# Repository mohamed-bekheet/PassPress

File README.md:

# PassPress (Hardware Security & BLE Keyboard Project)

**PassPress** is an open hardware and software project featuring a compact hardware password manager and custom Bluetooth Low Energy (BLE) / USB HID keyboard device.

---

## Repository Structure (Monorepo)

This repository is organized as a unified monorepo containing all sub-systems of the project:

```
Pass_Press/
├── passpress-hardware/     # PCB schematics (KiCad), BOM Excel sheet, datasheets, libraries
├── passpress-firmware/     # Embedded C/C++ firmware (STM32F042), USB HID, Bootloader, GUI
├── passpress_mobile_ble/   # Android BLE virtual keyboard app & companion software
├── passpress-huawei-watch/ # Huawei wearable watch companion application
└── README.md               # Root project index (this file)
```

---

## Component Quick Links

1. 🛠️ **[Hardware (`passpress-hardware`)](file:///e:/Personal/Pass_Press/passpress-hardware/README.md)**:
   - KiCad schematics and PCB designs for STM32 and CH32 MCU variants (`kicad-stm`, `kicad-ch32`, `kicad-v2`).
   - Bill of Materials ([Components.xlsx](file:///e:/Personal/Pass_Press/passpress-hardware/Components.xlsx)).
   - IC Datasheets ([datasheets/](file:///e:/Personal/Pass_Press/passpress-hardware/datasheets/)).

2. ⚡ **[Embedded Firmware (`passpress-firmware`)](file:///e:/Personal/Pass_Press/passpress-firmware/README.md)**:
   - STM32F042 C/C++ firmware workspace (`STM_WS`).
   - USB HID driver, Bootloader, Touch sensing (`TOUCHSENSING`), and GUI display engine.

3. 📱 **[Mobile Application (`passpress_mobile_ble`)](file:///e:/Personal/Pass_Press/passpress_mobile_ble/README.md)**:
   - Native Android Virtual BLE Keyboard app (`android/passpress_ble_keyboard`).
   - Setup guide ([ANDROID_SETUP.md](file:///e:/Personal/Pass_Press/passpress_mobile_ble/ANDROID_SETUP.md)).
   - Legacy Web Bluetooth and Python testing tools (`legacy/`).

4. ⌚ **[Huawei Watch App (`passpress-huawei-watch`)](file:///e:/Personal/Pass_Press/passpress-huawei-watch/README.md)**:
   - Huawei smartwatch companion app for HarmonyOS / LiteOS / Huawei Wear Engine.

---

## Project Architecture Summary

```
+------------------------+      BLE / USB      +-------------------------+
|  passpress_mobile_ble  |  ---------------->  |   passpress-hardware    |
|  (Android Companion)   |                     |   (PCB, MCU, Touch, USB)  |
+------------------------+                     +-------------------------+
                                                            |
                                                            v
                                               +-------------------------+
                                               |   passpress-firmware    |
                                               |  (C/C++, USB HID, GUI)  |
                                               +-------------------------+
```

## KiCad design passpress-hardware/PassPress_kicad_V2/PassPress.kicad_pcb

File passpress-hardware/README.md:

# PassPress Hardware (`passpress-hardware`)

Welcome to the **PassPress Hardware** design repository. This directory contains the complete electronic engineering files for the PassPress hardware device, including KiCad schematics, PCB layout files, component libraries, datasheet references, and Bill of Materials (BOM).

---

## Directory Structure

```
passpress-hardware/
├── PassPress_kicad/           # Main base PCB schematic and board layout
├── PassPress_kicad_STM/       # PCB design variant for STM32 microcontroller
├── PassPress_kicad_CH32/      # PCB design variant for CH32 microcontroller
├── PassPress_kicad_CH32_BLE/  # PCB design variant for CH32 BLE microcontroller
├── PassPress_kicad_Combined/  # Combined hardware schematic & PCB layout
├── PassPress_kicad_V2/        # Hardware Revision 2 schematic and layout
├── datasheets/                # Technical IC datasheets & component specifications
├── STM_DOC/                   # STM microcontroller documentation & reference manuals
├── libs_ripos/                # KiCad custom symbol & footprint libraries
├── Components.xlsx            # Master Bill of Materials (BOM) & component list
└── README.md                  # This documentation file
```

---

## Hardware Modules & Schematic Hierarchy

Each KiCad project directory contains structured schematic sheets for specific hardware functional blocks:

- `mcu.kicad_sch` — Main Microcontroller circuit (STM32 / CH32) & pin assignments.
- `power.kicad_sch` — Power management, voltage regulators, and battery/LDO circuit.
- `usb.kicad_sch` — USB Type-C interface, ESD protection, and data line conditioning.
- `antenna.kicad_sch` — Bluetooth LE antenna matching network & RF frontend.
- `INTERFACE.kicad_sch` — User input buttons, touch sensor pads, and display connectors.

---

## Microcontroller Variants

1. **STM32 Variant (`PassPress_kicad_STM`)**:
   - Target MCU: STM32F042 ARM Cortex-M0.
   - Built-in USB 2.0 Full-Speed Crystal-less controller & capacitive touch sensing logic.

2. **CH32 / CH32-BLE Variant (`PassPress_kicad_CH32`, `PassPress_kicad_CH32_BLE`)**:
   - Target MCU: WCH CH32 series microcontroller with integrated BLE transceiver.

---

## Inventory & Component Data

- **Master BOM**: Refer to [Components.xlsx](file:///e:/Personal/Pass_Press/passpress-hardware/Components.xlsx) for part numbers, manufacturer details, and package sizes (e.g. 0603, QFN, QFP).
- **Datasheets**: Refer to the [datasheets/](file:///e:/Personal/Pass_Press/passpress-hardware/datasheets/) directory for hardware datasheets.

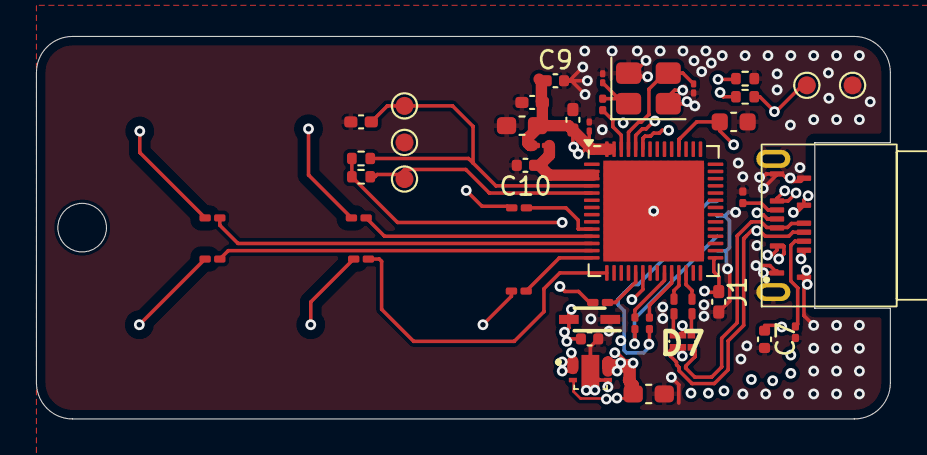
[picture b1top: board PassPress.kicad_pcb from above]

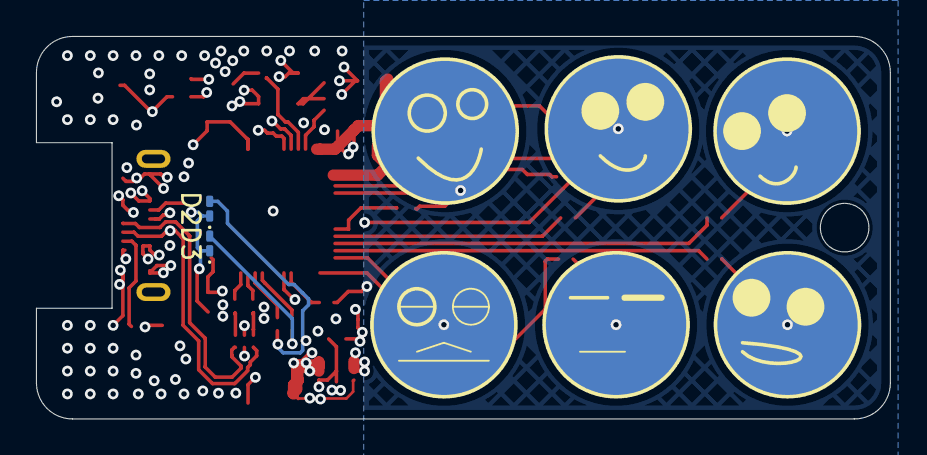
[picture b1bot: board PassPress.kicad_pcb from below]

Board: 4 copper layers, 47.4 x 21.2 mm, 53 parts (8 on the bottom side), 36 nets.

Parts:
C3: 10uF; C_0603_1608Metric_Pad1.08x0.95mm_HandSolder
C4: 0.1u; C_0603_1608Metric
C5, C6, C11, C21: 1u; C_0402_1005Metric_Pad0.74x0.62mm_HandSolder
C7, C9, C10: 0.1uF; C_0402_1005Metric
C8: 10n; C_01005_0402Metric
C13: 22uF; C_0603_1608Metric_Pad1.08x0.95mm_HandSolder
C15, C16: 22pF; C_01005_0402Metric
C20: 4.7uF; C_0402_1005Metric
D1: PESD3V3L1BAF; SOD2512X110N
D2, D3: LED; LED_0201_0603Metric_Pad0.64x0.40mm_HandSolder
D7: PRTR5V0U2F,115; PESD3V3L5UF115
H1: MountingHole; MountingHole_2.7mm
IC2: XC6220B331ER-G
J1: USB_C_GT-USB-8012A
L1: 2n; L_01005_0402Metric
L2: 24nH; L_0201_0603Metric
R1, R2: 5.1K; R_0201_0603Metric
R3, R4, R7, R8: 10K; R_0402_1005Metric
R5, R6: 22R; R_0201_0603Metric_Pad0.64x0.40mm_HandSolder
R9, R10, R11, R12, R13, R14, R15: 510R; R_0201_0603Metric_Pad0.64x0.40mm_HandSolder
R16, R17: 220R; R_0201_0603Metric
TP1: RST; TestPoint_Pad_D1.0mm
TP2: RST-G; TestPoint_Pad_D1.0mm
TP6: TestPoint; TestPoint_Pad_D1.0mm
TP7: BOOT-G; TestPoint_Pad_D1.0mm
TP8: BOOT; TestPoint_Pad_D1.0mm
TP11: TOUCH_PAD_1
TP12: TOUCH_PAD_1; TOUCH_PAD_2
TP13: TOUCH_PAD_1; TOUCH_PAD_3
TP14: TOUCH_PAD_1; TOUCH_PAD_4
TP15: TOUCH_PAD_1; TOUCH_PAD_5
TP16: TOUCH_PAD_1; TOUCH_PAD_6
U6: ESP32-S3; QFN-56-1EP_7x7mm_P0.4mm_EP5.6x5.6mm
X1: 40MHZ; Crystal_SMD_3225-4Pin_3.2x2.5mm

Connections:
5V: C13.1, IC2.3 (CE), IC2.5 (VIN_1), IC2.6 (VIN_2), J1.A4 (VBUS), J1.A9 (VBUS), J1.B4 (VBUS), J1.B9 (VBUS)
+3.3V: C3.1, C4.1, C5.1, C6.1, C7.1, C8.1, C9.1, C11.1, C20.1, D1.2 (K2), D7.5 (supply_voltage), IC2.1 (VOUT_1), IC2.2 (VOUT_2), L1.1, R3.1, R4.1, R8.1, TP6.1, U6.20 (VDD3P3_RTC), U6.29 (VDD_SPI), U6.46 (VDD3P3_CPU), U6.55 (VDDA), U6.56 (VDDA)
/MCU/BOOT0: R4.2, TP8.1, U6.5 (GPIO0/BOOT)
/MCU/D+: R5.1, U6.26 (GPIO20/USB_D+/ADC2_CH9)
/MCU/D-: R6.1, U6.25 (GPIO19/USB_D-/ADC2_CH8)
/MCU/LED1-B: R16.2, U6.24 (GPIO18/ADC2_CH7)
/MCU/LED2-G: R17.2, U6.23 (GPIO17/ADC2_CH6)
/MCU/PRESS1: R9.2, TP11.1
/MCU/PRESS2: R10.2, TP12.1
/MCU/PRESS3: R11.2, TP13.1
/MCU/PRESS4: R12.2, TP14.1
/MCU/PRESS5: R13.2, TP15.1
/MCU/PRESS6: R14.2, TP16.1
/MCU/RST: C21.1, R3.2, TP1.1, U6.4 (CHIP_PU/RESET)
/MCU/XTAL_N: C16.1, U6.53 (XTAL_N), X1.3
/MCU/XTAL_P: C15.1, L2.1, X1.1
/USB-C/ESD_USB_D+: D7.3 (input/output_2_1), J1.A7 (D-), J1.B7 (D-)
/USB-C/ESD_USB_D-: D7.1 (input/output_1_1), J1.A6 (D+), J1.B6 (D+)
/USB-C/USB_D+: D7.4 (input/output_2_2), R5.2
/USB-C/USB_D-: D7.6 (input/output_1_2), R6.2
GND: C3.2, C4.2, C5.2, C6.2, C7.2, C8.2, C9.2, C10.2, C11.2, C13.2, C15.2, C16.2, C20.2, C21.2, D1.1 (K1), D2.1 (K), D3.1 (K), D7.2 (ground), IC2.4 (VSS), IC2.7 (EP), J1.A1 (GND), J1.A12 (GND), J1.B1 (GND), J1.B12 (GND), J1.S1 (SHIELD), R1.2, R2.2, R7.2, TP2.1, TP7.1, U6.57 (GND), X1.2, X1.4
unnamed: D2.2 (A), R16.1
unnamed: D3.2 (A), R17.1
unnamed: J1.A5 (CC1), R2.1
unnamed: J1.B5 (CC2), R1.1
unnamed: R9.1, U6.10 (GPIO5/ADC1_CH4)
unnamed: R10.1, U6.11 (GPIO6/ADC1_CH5)
unnamed: R11.1, U6.12 (GPIO7/ADC1_CH6)
unnamed: R12.1, U6.13 (GPIO8/ADC1_CH7)
unnamed: R13.1, U6.14 (GPIO9/ADC1_CH8)
unnamed: R14.1, U6.15 (GPIO10/ADC1_CH9)
unnamed: R15.1, U6.19 (GPIO14/ADC2_CH3)
unnamed: R8.2, U6.51 (GPIO45)
unnamed: R7.1, U6.52 (GPIO46)
unnamed: L2.2, U6.54 (XTAL_P)
VDD3P3: C10.1, L1.2, U6.2 (VDD3P3), U6.3 (VDD3P3)

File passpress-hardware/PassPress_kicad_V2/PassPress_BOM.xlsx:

Id | Designator | Footprint | Quantity | Designation | MNF PART NUMBER
1 | C13 | C_0603_1608Metric_Pad1.08x0.95mm_HandSolder | 1 | 22uF | C59461
2 | C14,C4,C10,C9,C7 | C_0402_1005Metric | 1 | 0.1uF | C1525
3 | C16,C15 | C_01005_0402Metric | 2 | 22pF | C1555
4 | C20 | C_0402_1005Metric | 1 | 4.7uF | C23733
5 | C3 | C_0603_1608Metric_Pad1.08x0.95mm_HandSolder | 1 | 10uF | C19702
6 | C5,C21,C11,C6 | C_0402_1005Metric_Pad0.74x0.62mm_HandSolder | 4 | 1uF | C52923
7 | C8 | C_01005_0402Metric | 1 | 10nF | C15195
8 | D1 | SOD2512X110N | 1 | PESD3V3L1BAF | C552512
9 | D3 | LED_0201_0603Metric_Pad0.64x0.40mm_HandSolder | 2 | LED | C3646921
10 | D2 | LED_0201_0603Metric_Pad0.64x0.40mm_HandSolder | 2 | LED | C3646922
11 | D7 | PESD3V3L5UF115 | 1 | PRTR5V0U2F,115 | C2937001
12 | IC2 | XC6220B331ER-G | 1 | XC6220B331ER-G | C3013657
13 | J1 | USB_C_GT-USB-8012A | 1 | USB_C_GT-USB-8012A | C2982483
14 | L1 | L_01005_0402Metric | 1 | 2n | C18216
15 | L2 | L_0201_0603Metric | 1 | 24nH | C206441
16 | R1,R2 | R_0201_0603Metric | 2 | 5.1K | C163490
17 | R14,R12,R10,R15,R9,R11,R13 | R_0201_0603Metric_Pad0.64x0.40mm_HandSolder | 7 | 510R | C57784
18 | R16,R17 | R_0201_0603Metric | 2 | 220R | C144009
19 | R3,R8,R7,R4 | R_0402_1005Metric | 4 | 10K | C25744
20 | R5,R6 | R_0201_0603Metric_Pad0.64x0.40mm_HandSolder | 2 | 22R | C100162
21 | U6 | QFN-56-1EP_7x7mm_P0.4mm_EP5.6x5.6mm | 1 | ESP32-S3FH4R2 | C3013940
22 | X1 | Crystal_SMD_3225-4Pin_3.2x2.5mm | 1 | XL2EL89CPI-111YLC-40M | C5444549

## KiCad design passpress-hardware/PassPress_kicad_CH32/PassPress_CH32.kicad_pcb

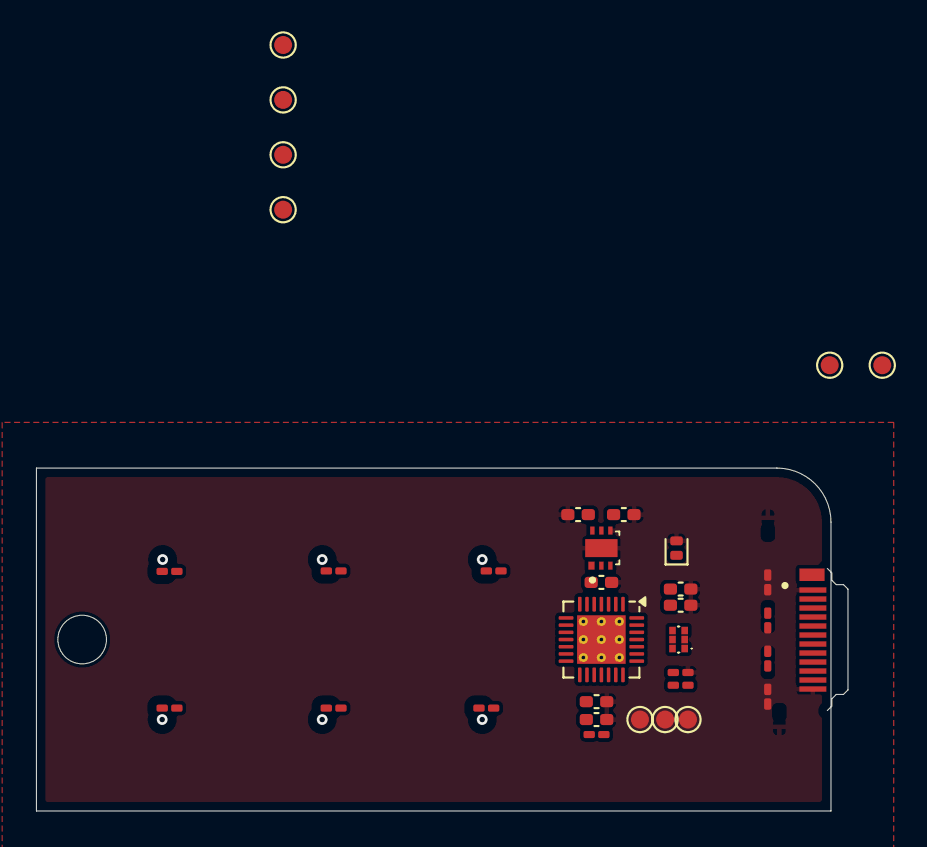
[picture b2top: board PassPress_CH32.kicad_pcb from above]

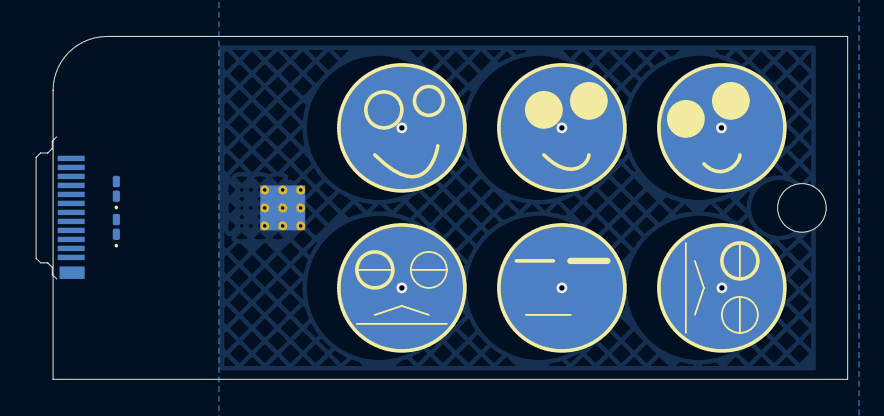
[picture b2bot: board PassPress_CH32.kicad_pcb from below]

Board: 4 copper layers, 45.1 x 19.0 mm, 43 parts (8 on the bottom side), 29 nets, no tracks yet.

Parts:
C3, C20: 4.7uF; C_0402_1005Metric_Pad0.74x0.62mm_HandSolder
C5, C6: 0.1uF; C_0402_1005Metric_Pad0.74x0.62mm_HandSolder
C7: 10n; C_0402_1005Metric_Pad0.74x0.62mm_HandSolder
C11: 1uF; C_0402_1005Metric_Pad0.74x0.62mm_HandSolder
C13: 22uF; C_0402_1005Metric_Pad0.74x0.62mm_HandSolder
D2: LED-R; LED_0201_0603Metric_Pad0.64x0.40mm_HandSolder
D3: LED-G; LED_0201_0603Metric_Pad0.64x0.40mm_HandSolder
D4: PESD5V0V1BL,315; D_SOD-882D
D7: PRTR5V0U2F,115; PESD3V3L5UF115
H1: MountingHole; MountingHole_2.7mm
IC2: XC6220B331ER-G
J1: U261-241N-4BS60; XKB_U261-241N-4BS60_USB_C
R2, R7, R8, R9, R10, R11, R12, R13: 5.1K; R_0201_0603Metric_Pad0.64x0.40mm_HandSolder
R3, R4, R5: 10K; R_0201_0603Metric_Pad0.64x0.40mm_HandSolder
R6, R16: 220R; R_0201_0603Metric_Pad0.64x0.40mm_HandSolder
TP1: RST; TestPoint_Pad_D1.0mm
TP2: RST-G; TestPoint_Pad_D1.0mm
TP5: 3.3V; TestPoint_Pad_D1.0mm
TP6: TestPoint; TestPoint_Pad_D1.0mm
TP7: BOOT-G; TestPoint_Pad_D1.0mm
TP8: BOOT; TestPoint_Pad_D1.0mm
TP11: TOUCH_PAD_1; TOUCH_PAD_1_7mm
TP12: TOUCH_PAD_1; TOUCH_PAD_2_7mm
TP13: TOUCH_PAD_1; TOUCH_PAD_3_7mm
TP14: TOUCH_PAD_1; TOUCH_PAD_4_7mm
TP15: TOUCH_PAD_1; TOUCH_PAD_5_7mm
TP16: TOUCH_PAD_1; TOUCH_PAD_6_7mm
TP19: SWDIO; TestPoint_Pad_D1.0mm
TP20: SWCLK; TestPoint_Pad_D1.0mm
TP21: GND; TestPoint_Pad_D1.0mm
U2: CH32X035G8U6; WQFN-28-1EP_4x4mm_P0.4mm_EP2.7x2.7mm_ThermalVias

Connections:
5V: C3.1, C13.1, D4.1 (K), IC2.3 (CE), IC2.5 (VIN_1), IC2.6 (VIN_2), J1.A4 (VBUS), J1.A9 (VBUS), J1.B4 (VBUS), J1.B9 (VBUS)
+3.3V: C5.1, C11.1, C20.1, D7.5 (supply_voltage), IC2.1 (VOUT_1), IC2.2 (VOUT_2), R3.1, R5.1, TP5.1, TP6.1, TP7.1, U2.2 (VDD)
/MCU/BOOT0: R4.1, R5.2, TP8.1, TP20.1, U2.24 (PC19/DCK)
/MCU/D+: D7.4 (input/output_2_2), U2.27 (PC10/PC17/UDP)
/MCU/D-: D7.6 (input/output_1_2), U2.26 (PC11/PC16/UDM)
/MCU/LED1-B: R16.2, U2.3 (PC0)
/MCU/LED2-G: R6.2, U2.16 (PB1/PB5)
/MCU/P1: R8.1, U2.6 (PA1)
/MCU/P2: R9.1, U2.7 (PA2)
/MCU/P3: R10.1, U2.8 (PA3)
/MCU/P4: R11.1, U2.9 (PA4)
/MCU/P5: R12.1, U2.11 (PA6)
/MCU/P6: R13.1, U2.10 (PA5)
/MCU/PRESS1: R8.2, TP11.1
/MCU/PRESS2: R9.2, TP12.1
/MCU/PRESS3: R10.2, TP13.1
/MCU/PRESS4: R11.2, TP14.1
/MCU/PRESS5: R12.2, TP15.1
/MCU/PRESS6: R13.2, TP16.1
/MCU/RST: C6.1, R3.2, TP1.1, U2.4 (PC3)
/MCU/SWDIO: TP19.1, U2.25 (PC18/DIO)
/USB-C/ESD_USB_D+: D7.3 (input/output_2_1), J1.A7 (D-), J1.B7 (D-)
/USB-C/ESD_USB_D-: D7.1 (input/output_1_1), J1.A6 (D+), J1.B6 (D+)
GND: C3.2, C5.2, C6.2, C7.2, C11.2, C13.2, C20.2, D2.1 (K), D3.1 (K), D4.2 (A), D7.2 (ground), IC2.4 (VSS), IC2.7 (EP), J1.A1 (GND), J1.A12 (GND), J1.B1 (GND), J1.B12 (GND), R2.2, R4.2, R7.2, TP2.1, TP21.1, U2.29 (GND)
unnamed: D2.2 (A), R6.1
unnamed: D3.2 (A), R16.1
unnamed: J1.A5 (CC1), R2.1
unnamed: J1.B5 (CC2), R7.1
unnamed: C7.1, U2.5 (PA0)

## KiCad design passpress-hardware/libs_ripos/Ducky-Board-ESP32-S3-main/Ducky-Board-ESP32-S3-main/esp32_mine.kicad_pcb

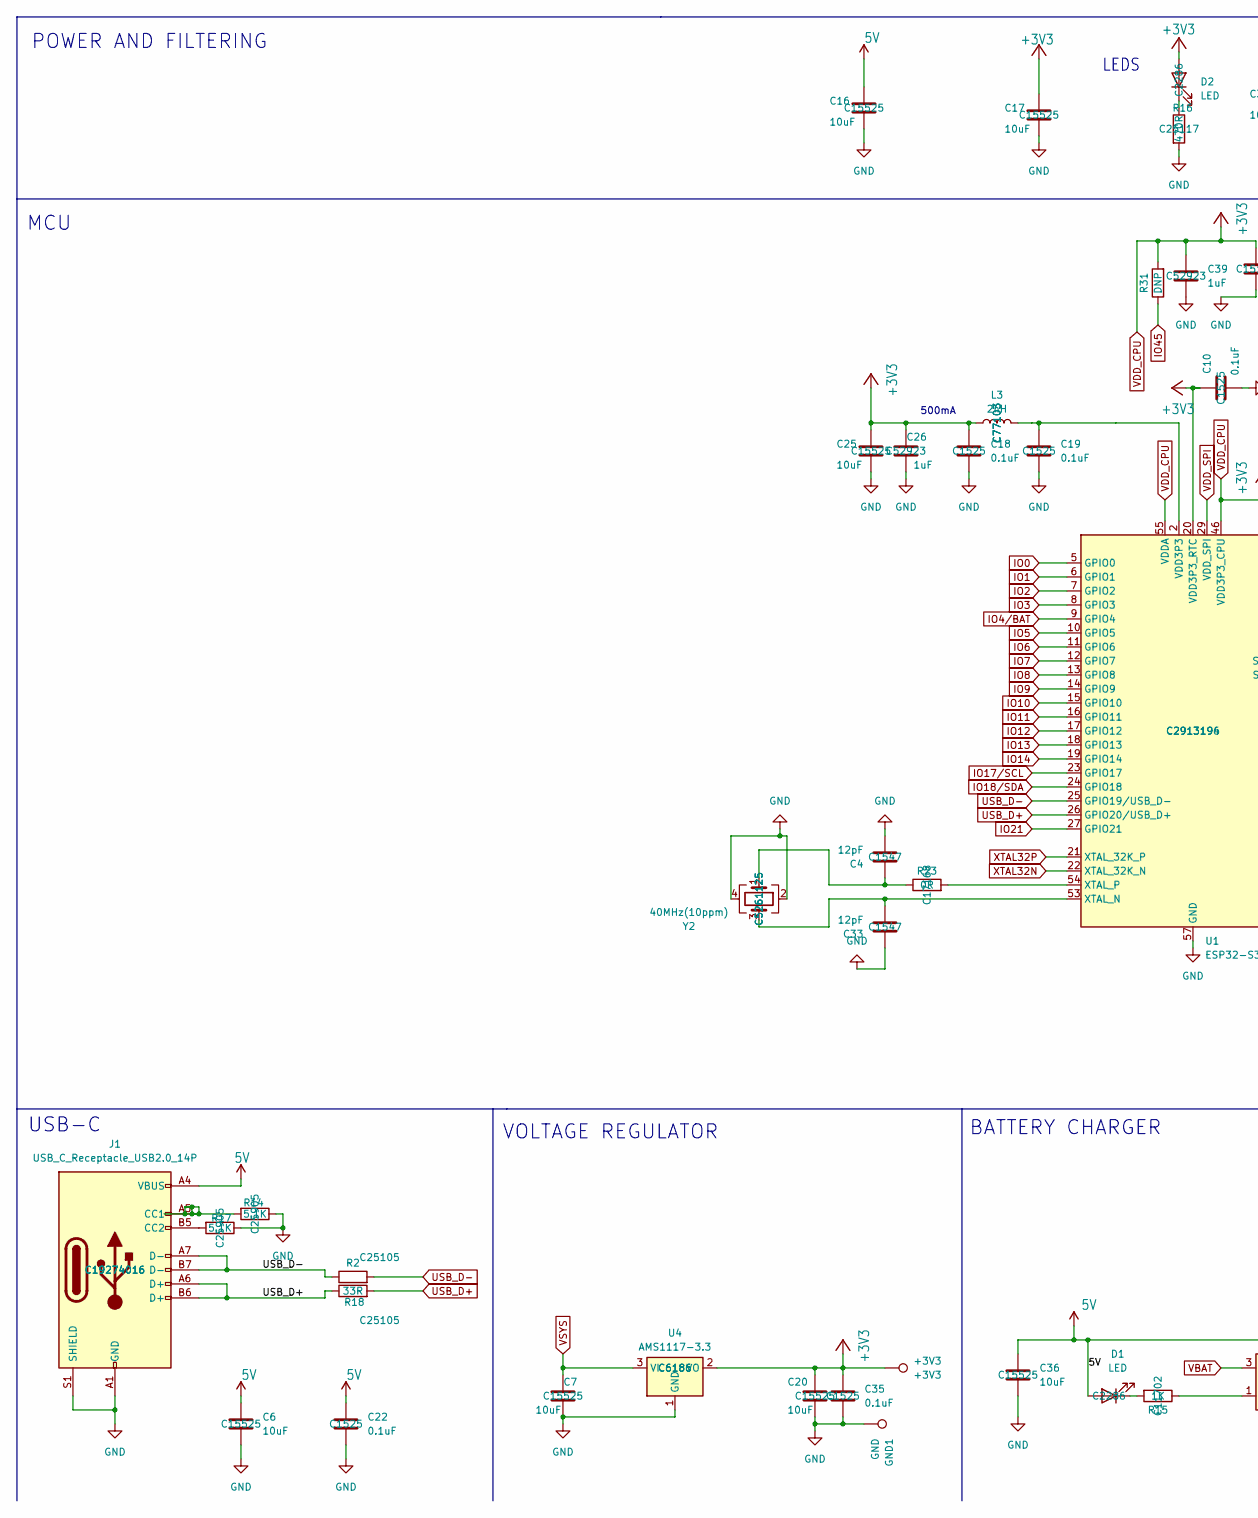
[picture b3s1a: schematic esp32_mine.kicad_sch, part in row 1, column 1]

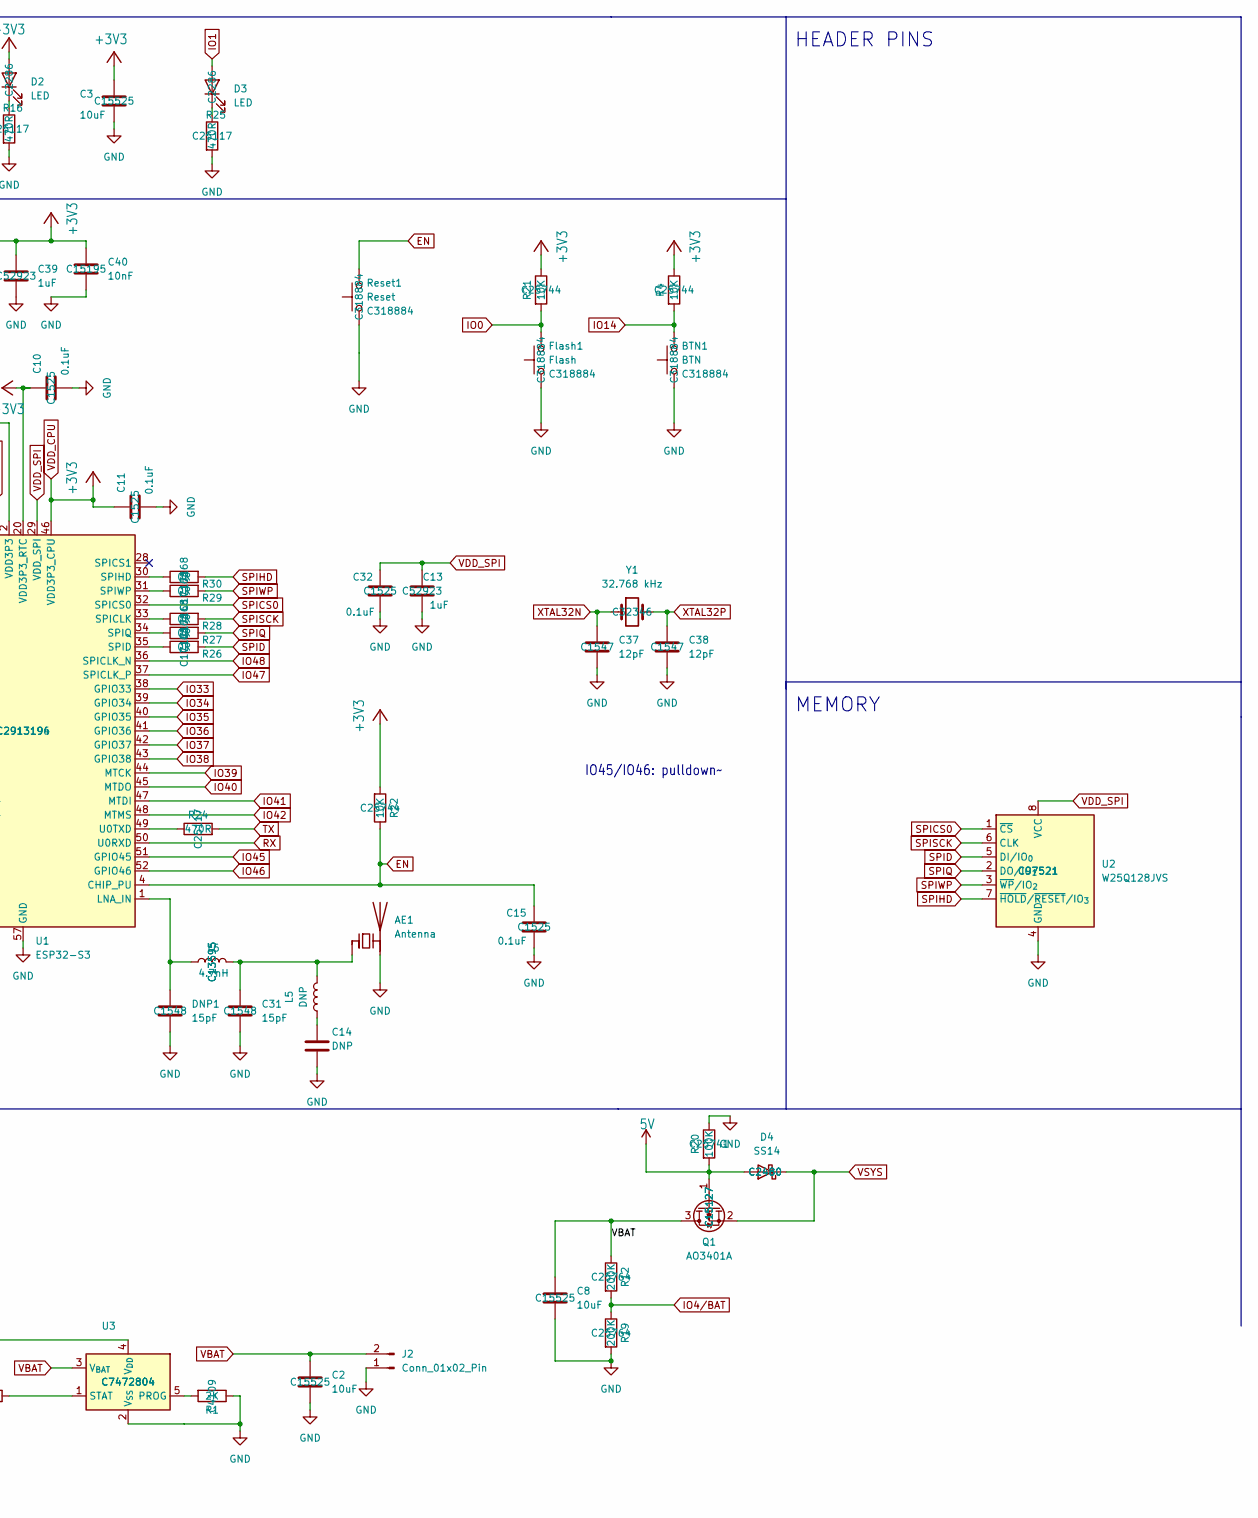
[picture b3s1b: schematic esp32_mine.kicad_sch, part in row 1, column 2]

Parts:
+3V3: +3V3; TestPoint_Pad_D1.0mm
AE1: Antenna; Texas_SWRA117D_2.4GHz_Left
BTN1: BTN; SW_Push_1P1T_XKB_TS-1187A; MNF PART NUMBER C318884; LCSC C318884
C2, C3, C6, C7, C8, C16, C17, C20, C25, C36: 10uF; C_0402_1005Metric; MNF PART NUMBER C15525; LCSC C15525
C4, C33, C37, C38: 12pF; C_0402_1005Metric; MNF PART NUMBER C1547; LCSC C1547
C10, C11, C15, C18, C19, C22, C32, C35: 0.1uF; C_0402_1005Metric; MNF PART NUMBER C1525; LCSC C1525
C13, C26, C39: 1uF; C_0402_1005Metric; MNF PART NUMBER C52923; LCSC C52923
C14: DNP; C_0402_1005Metric
C31: 15pF; C_0402_1005Metric; MNF PART NUMBER C1548; LCSC C1548
C40: 10nF; C_0402_1005Metric; MNF PART NUMBER C15195; LCSC C15195
D1, D2, D3: LED; LED_0603_1608Metric; MNF PART NUMBER C2286; LCSC C2286
D4: SS14; D_SMA; MNF PART NUMBER C2480; LCSC C2480
DNP1: 15pF; C_0402_1005Metric; MNF PART NUMBER C1548; LCSC C1548
Flash1: Flash; SW_Push_1P1T_XKB_TS-1187A; MNF PART NUMBER C318884; LCSC C318884
GND1: GND; TestPoint_Pad_D1.0mm
J1: USB_C_Receptacle_USB2.0_14P; USB_C_Receptacle_HCTL_HC-TYPE-C-16P-01A; MNF PART NUMBER C19274016; LCSC C19274016
J2: Conn_01x02_Pin; PinSocket_1x02_P2.54mm_Vertical
L3: 2nH; L_0402_1005Metric; MNF PART NUMBER C77103; LCSC C77103
L5: DNP; L_0402_1005Metric
L6: 4.7nH; L_0402_1005Metric; MNF PART NUMBER C13595; LCSC C13595
Q1: AO3401A; SOT-23; MNF PART NUMBER C15127; LCSC C15127
R1: 2K; R_0402_1005Metric; MNF PART NUMBER C4109; LCSC C4109
R2, R18: 33R; R_0402_1005Metric; MNF PART NUMBER C25105; LCSC C25105
R4, R21, R22: 10K; R_0402_1005Metric; MNF PART NUMBER C25744; LCSC C25744
R12, R19: 200K; R_0402_1005Metric; MNF PART NUMBER C25764; LCSC C25764
R14, R17: 5.1K; R_0402_1005Metric; MNF PART NUMBER C25905; LCSC C25905
R15: 1K; R_0402_1005Metric; MNF PART NUMBER C11702; LCSC C11702
R16, R24, R25: 470R; R_0402_1005Metric; MNF PART NUMBER C25117; LCSC C25117
R20: 100K; R_0402_1005Metric; MNF PART NUMBER C25741; LCSC C25741
R23, R26, R27, R28, R29, R30: 0R; R_0402_1005Metric; MNF PART NUMBER C17168; LCSC C17168
R31: DNP; R_0402_1005Metric
Reset1: Reset; SW_Push_1P1T_XKB_TS-1187A; MNF PART NUMBER C318884; LCSC C318884
U1: ESP32-S3; QFN-56-1EP_7x7mm_P0.4mm_EP4x4mm; MNF PART NUMBER C2913196; LCSC C2913194
U2: W25Q128JVS; SOIC-8_5.3x5.3mm_P1.27mm; MNF PART NUMBER C97521; LCSC C97521
U3: MCP73831-2-OT; SOT-23-5; MNF PART NUMBER C7472804; LCSC C7472804
U4: AMS1117-3.3; SOT-223-3_TabPin2; MNF PART NUMBER C6186; LCSC C6186
Y1: 32.768 kHz; Crystal_SMD_3215-2Pin_3.2x1.5mm; MNF PART NUMBER C32346; LCSC C32346
Y2: 40MHz(10ppm); Crystal_SMD_2520-4Pin_2.5x2.0mm; MNF PART NUMBER C5261125; LCSC C5261125

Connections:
5V: C6.1, C16.1, C22.1, C36.1, D1.2 (A), D4.2 (A), J1.A4 (VBUS), J1.A9 (VBUS), J1.B4 (VBUS), J1.B9 (VBUS), Q1.1 (G), R20.2, U3.4 (V_{DD}); also elsewhere on the board
EN: C15.1, R22.1, Reset1.2, U1.4 (CHIP_PU)
GND: AE1.2 (PCB_Trace), BTN1.1, C2.2, C3.2, C4.2, C6.2, C7.2, C8.2, C10.2, C11.2, C13.2, C14.2, C15.2, C16.2, C17.2, C18.2, C19.2, C20.2, C22.2, C25.2, C26.2, C31.2, C32.2, C33.1, C35.2, C36.2, C37.2, C38.2, C39.2, C40.2, DNP1.2, Flash1.1, GND1.1, J1.A1 (GND), J1.A12 (GND), J1.B1 (GND), J1.B12 (GND), J1.S1 (SHIELD), J2.1, R1.1, R14.1, R16.2, R17.1, R19.2, R20.1, R25.2, Reset1.1, U1.57 (GND), U2.4 (GND), U3.2 (V_{SS}), U4.1 (GND), Y2.2, Y2.4; also elsewhere on the board
IO0: Flash1.2, R21.2, U1.5 (GPIO0); also elsewhere on the board
IO1: D3.2 (A), U1.6 (GPIO1)
IO2: U1.7 (GPIO2); also elsewhere on the board
IO3: U1.8 (GPIO3); also elsewhere on the board
IO4/BAT: R12.2, R19.1, U1.9 (GPIO4)
IO5: U1.10 (GPIO5); also elsewhere on the board
IO6: U1.11 (GPIO6); also elsewhere on the board
IO7: U1.12 (GPIO7); also elsewhere on the board
IO8: U1.13 (GPIO8); also elsewhere on the board
IO9: U1.14 (GPIO9); also elsewhere on the board
IO10: U1.15 (GPIO10); also elsewhere on the board
IO11: U1.16 (GPIO11); also elsewhere on the board
IO12: U1.17 (GPIO12); also elsewhere on the board
IO13: U1.18 (GPIO13); also elsewhere on the board
IO14: BTN1.2, R4.2, U1.19 (GPIO14); also elsewhere on the board
IO17/SCL: U1.23 (GPIO17); also elsewhere on the board
IO18/SDA: U1.24 (GPIO18); also elsewhere on the board
IO21: U1.27 (GPIO21); also elsewhere on the board
IO33: U1.38 (GPIO33); also elsewhere on the board
IO34: U1.39 (GPIO34); also elsewhere on the board
IO35: U1.40 (GPIO35); also elsewhere on the board
IO36: U1.41 (GPIO36); also elsewhere on the board
IO37: U1.42 (GPIO37); also elsewhere on the board
IO38: U1.43 (GPIO38); also elsewhere on the board
IO39: U1.44 (MTCK); also elsewhere on the board
IO40: U1.45 (MTDO); also elsewhere on the board
IO41: U1.47 (MTDI); also elsewhere on the board
IO42: U1.48 (MTMS); also elsewhere on the board
IO45: R31.1, U1.51 (GPIO45); also elsewhere on the board
IO46: U1.52 (GPIO46); also elsewhere on the board
IO47: U1.37 (SPICLK_P); also elsewhere on the board
IO48: U1.36 (SPICLK_N); also elsewhere on the board
unnamed: AE1.1 (FEED), C31.1, L5.2, L6.2
unnamed: C4.1, R23.1, Y2.1
unnamed: C14.1, L5.1
unnamed: C19.1, L3.2, U1.2 (VDD3P3), U1.3 (VDD3P3)
unnamed: D1.1 (K), R15.2
unnamed: D2.1 (K), R16.1
unnamed: D3.1 (K), R25.1
unnamed: J1.A5 (CC1), R14.2
unnamed: J1.B5 (CC2), R17.2
unnamed: DNP1.1, L6.1, U1.1 (LNA_IN)
unnamed: R28.1, U1.33 (SPICLK)
unnamed: R26.1, U1.35 (SPID)
unnamed: R30.1, U1.30 (SPIHD)
unnamed: R27.1, U1.34 (SPIQ)
unnamed: R29.1, U1.31 (SPIWP)
unnamed: R24.1, U1.49 (U0TXD)
unnamed: C33.2, U1.53 (XTAL_N), Y2.3
unnamed: R23.2, U1.54 (XTAL_P)
unnamed: R1.2, U3.5 (PROG)
unnamed: R15.1, U3.1 (STAT)
RX: U1.50 (U0RXD); also elsewhere on the board
SPICS0: U1.32 (SPICS0), U2.1 (~CS)
SPID: R26.2, U2.5 (DI/IO_{0})
SPIHD: R30.2, U2.7 (~HOLD/~RESET/IO_{3})
SPIQ: R27.2, U2.2 (DO/IO_{1})
SPISCK: R28.2, U2.6 (CLK)
SPIWP: R29.2, U2.3 (~WP/IO_{2})
TX: R24.2; also elsewhere on the board
USB_D+: J1.A6 (D+), J1.B6 (D+), R18.1, R18.2, U1.26 (GPIO20/USB_D+)
USB_D-: J1.A7 (D-), J1.B7 (D-), R2.1, R2.2, U1.25 (GPIO19/USB_D-)
VBAT: C2.1, C8.1, J2.2, Q1.3 (D), R12.1, U3.3 (V_{BAT})
VDD_CPU: +3V3.1, C3.1, C10.1, C11.1, C17.1, C18.1, C20.1, C25.1, C26.1, C35.1, C39.1, C40.1, D2.2 (A), L3.1, R4.1, R21.1, R22.2, R31.2, U1.20 (VDD3P3_RTC), U1.46 (VDD3P3_CPU), U1.55 (VDDA), U1.56 (VDDA), U4.2 (VO); also elsewhere on the board
VDD_SPI: C13.1, C32.1, U1.29 (VDD_SPI), U2.8 (VCC)
VSYS: C7.1, D4.1 (K), Q1.2 (S), U4.3 (VI)
XTAL32N: C37.1, U1.22 (XTAL_32K_N), Y1.1
XTAL32P: C38.1, U1.21 (XTAL_32K_P), Y1.2

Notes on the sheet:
BATTERY CHARGER
VOLTAGE REGULATOR
500mA
LEDS
MCU
HEADER PINS
MEMORY
POWER AND FILTERING
IO45/IO46: pulldown~~{}
USB-C

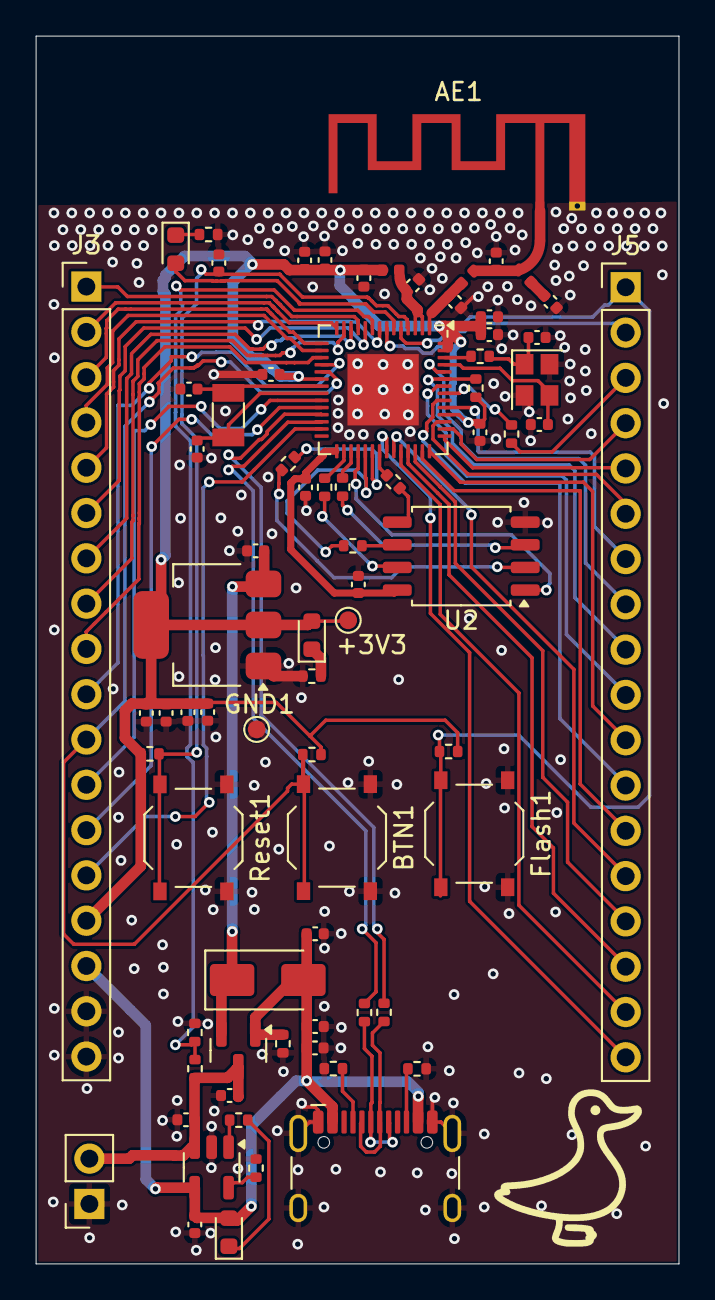
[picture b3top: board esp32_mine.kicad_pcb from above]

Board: 2 copper layers, 36.0 x 68.8 mm, 75 parts (0 on the bottom side), 71 nets.

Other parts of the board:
J3, J5: Conn_01x18_Pin; PinHeader_1x18_P2.54mm_Vertical

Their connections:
5V: J3.16; also elsewhere on the board
GND: J3.17, J3.18; also elsewhere on the board
IO0: J5.1; also elsewhere on the board
IO2: J5.2; also elsewhere on the board
IO3: J3.5; also elsewhere on the board
IO5: J3.6; also elsewhere on the board
IO6: J3.1; also elsewhere on the board
IO7: J3.7; also elsewhere on the board
IO8: J3.8; also elsewhere on the board
IO9: J3.2; also elsewhere on the board
IO10: J3.3; also elsewhere on the board
IO11: J3.4; also elsewhere on the board
IO12: J3.9; also elsewhere on the board
IO13: J3.10; also elsewhere on the board
IO14: J3.11; also elsewhere on the board
IO17/SCL: J3.12; also elsewhere on the board
IO18/SDA: J3.13; also elsewhere on the board
IO21: J3.14; also elsewhere on the board
IO33: J5.17; also elsewhere on the board
IO34: J5.16; also elsewhere on the board
IO35: J5.15; also elsewhere on the board
IO36: J5.13; also elsewhere on the board
IO37: J5.11; also elsewhere on the board
IO38: J5.5; also elsewhere on the board
IO39: J5.4; also elsewhere on the board
IO40: J5.6; also elsewhere on the board
IO41: J5.7; also elsewhere on the board
IO42: J5.12; also elsewhere on the board
IO45: J5.9; also elsewhere on the board
IO46: J5.8; also elsewhere on the board
IO47: J5.14; also elsewhere on the board
IO48: J5.18; also elsewhere on the board
RX: J5.10; also elsewhere on the board
TX: J5.3; also elsewhere on the board
VDD_CPU: J3.15; also elsewhere on the board

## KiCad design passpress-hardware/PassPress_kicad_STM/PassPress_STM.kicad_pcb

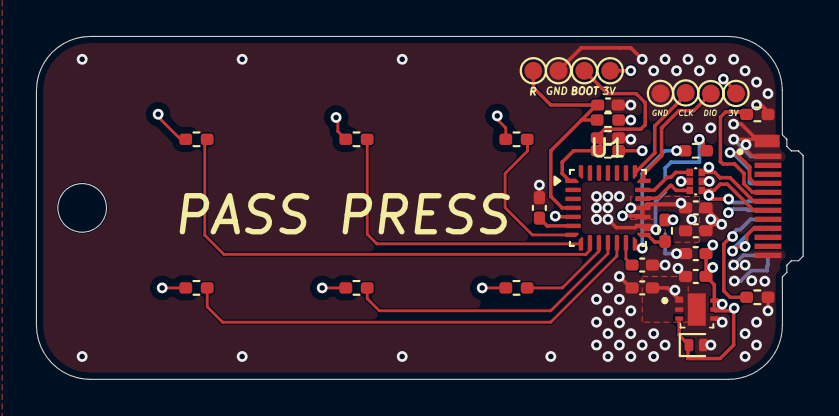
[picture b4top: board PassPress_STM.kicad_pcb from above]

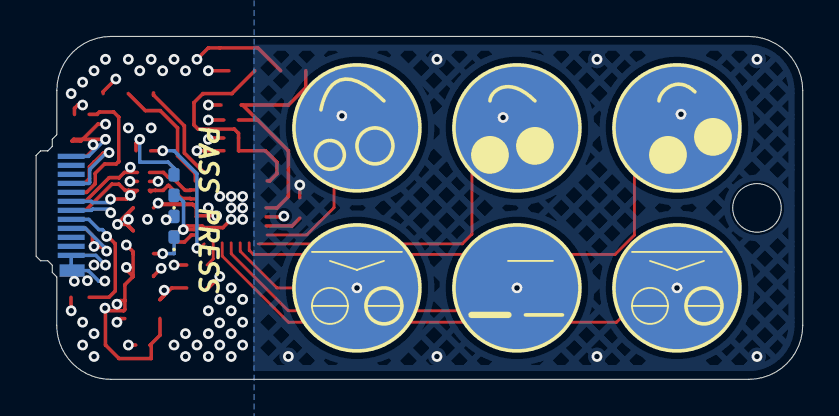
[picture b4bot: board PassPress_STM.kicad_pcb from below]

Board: 4 copper layers, 42.6 x 19.0 mm, 43 parts (8 on the bottom side), 31 nets.

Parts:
C3, C4, C20: 4.7uF; C_0402_1005Metric_Pad0.74x0.62mm_HandSolder
C6, C15: 0.1uF; C_0402_1005Metric_Pad0.74x0.62mm_HandSolder
C7, C8: 10n; C_0402_1005Metric_Pad0.74x0.62mm_HandSolder
C13: 22uF; C_0402_1005Metric_Pad0.74x0.62mm_HandSolder
D2: PESD5V0V1BL,315; D_SOD-882D
D4: LED-G; LED_0402_1005Metric_Pad0.77x0.64mm_HandSolder
D5: LED-R; LED_0402_1005Metric_Pad0.77x0.64mm_HandSolder
D7: PRTR5V0U2F,115; PESD3V3L5UF115
H1: MountingHole; MountingHole_2.7mm
IC2: XC6220B331ER-G
J1: U261-241N-4BS60; XKB_U261-241N-4BS60_USB_C
R1, R14: 220R; R_0402_1005Metric_Pad0.72x0.64mm_HandSolder
R2, R6, R7, R8, R9, R10, R11, R12: 5.1K; R_0402_1005Metric_Pad0.72x0.64mm_HandSolder
R3, R4, R5: 10K; R_0402_1005Metric_Pad0.72x0.64mm_HandSolder
TP1: RST; TestPoint_Pad_D1.0mm
TP2: RST-G; TestPoint_Pad_D1.0mm
TP5: 3.3V; TestPoint_Pad_D1.0mm
TP7: BOOT-G; TestPoint_Pad_D1.0mm
TP8: BOOT; TestPoint_Pad_D1.0mm
TP11: TOUCH_PAD_1; TOUCH_PAD_1_7mm
TP12: TOUCH_PAD_1; TOUCH_PAD_2_7mm
TP13: TOUCH_PAD_1; TOUCH_PAD_3_7mm
TP14: TOUCH_PAD_1; TOUCH_PAD_4_7mm
TP15: TOUCH_PAD_1; TOUCH_PAD_5_7mm
TP16: TOUCH_PAD_1; TOUCH_PAD_6_7mm
TP19: SWDIO; TestPoint_Pad_D1.0mm
TP20: SWCLK; TestPoint_Pad_D1.0mm
TP21: GND; TestPoint_Pad_D1.0mm
U1: STM32F042G6U6TR; QFN-28_4x4mm_P0.5mm

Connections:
5V: C3.1, C13.1, D2.1 (K), IC2.3 (CE), IC2.5 (VIN_1), IC2.6 (VIN_2), J1.A4 (VBUS), J1.A9 (VBUS), J1.B4 (VBUS), J1.B9 (VBUS)
+3.3V: C4.1, C15.1, C20.1, D7.5 (supply_voltage), IC2.1 (VOUT_1), IC2.2 (VOUT_2), R3.1, R5.1, TP5.1, TP7.1, U1.5 (VDDA), U1.17 (VDD), U1.18 (VDDIO2)
/MCU/BOOT0: R4.1, R5.2, TP8.1, U1.1 (PB8)
/MCU/D+: D7.4 (input/output_2_2), U1.20 (PA10/PA12)
/MCU/D-: D7.6 (input/output_1_2), U1.19 (PA9/PA11)
/MCU/LED1-B: R1.2, U1.14 (PB0)
/MCU/LED2-G: R14.2, U1.15 (PB1)
/MCU/P1: R8.1, U1.7 (PA1)
/MCU/P2: R9.1, U1.8 (PA2)
/MCU/P3: R10.1, U1.9 (PA3)
/MCU/P4: R11.1, U1.12 (PA6)
/MCU/P5: R12.1, U1.10 (PA4)
/MCU/P6: R6.1, U1.11 (PA5)
/MCU/PRESS1: R8.2, TP11.1
/MCU/PRESS2: R9.2, TP12.1
/MCU/PRESS3: R10.2, TP13.1
/MCU/PRESS4: R11.2, TP14.1
/MCU/PRESS5: R12.2, TP15.1
/MCU/PRESS6: R6.2, TP16.1
/MCU/RST: C6.1, R3.2, TP1.1, U1.4 (NRST)
/MCU/SWCLK: TP20.1, U1.22 (PA14)
/MCU/SWDIO: TP19.1, U1.21 (PA13)
/USB-C/ESD_USB_D+: D7.3 (input/output_2_1), J1.A6 (D+), J1.B6 (D+)
/USB-C/ESD_USB_D-: D7.1 (input/output_1_1), J1.A7 (D-), J1.B7 (D-)
GND: C3.2, C4.2, C6.2, C7.2, C8.2, C13.2, C15.2, C20.2, D2.2 (A), D4.1 (K), D5.1 (K), D7.2 (ground), IC2.4 (VSS), IC2.7 (EP), J1.A1 (GND), J1.A12 (GND), J1.B1 (GND), J1.B12 (GND), J1.S1 (SHIELD), R2.2, R4.2, R7.2, TP2.1, TP21.1, U1.16 (VSSA)
unnamed: D4.2 (A), R1.1
unnamed: D5.2 (A), R14.1
unnamed: J1.A5 (CC1), R2.1
unnamed: J1.B5 (CC2), R7.1
unnamed: C7.1, U1.6 (PA0)
unnamed: C8.1, U1.13 (PA7)

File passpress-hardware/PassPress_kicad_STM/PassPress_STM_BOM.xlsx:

Reference | Qty | Value | DNP | Exclude from BOM | Exclude from Board | Footprint | Datasheet | LCSC#
C3,C4,C20 | 3 | 4.7uF |  |  |  | Capacitor_SMD:C_0402_1005Metric_Pad0.74x0.62mm_HandSolder | ~ | C307423
C6,C15 | 2 | 0.1uF |  |  |  | Capacitor_SMD:C_0402_1005Metric_Pad0.74x0.62mm_HandSolder | ~ | C60474
C7,C8 | 2 | 10n |  |  |  | Capacitor_SMD:C_0402_1005Metric_Pad0.74x0.62mm_HandSolder | ~ | C53084509
C13 | 1 | 22uF |  |  |  | Capacitor_SMD:C_0402_1005Metric_Pad0.74x0.62mm_HandSolder | ~ | C415703
D2 | 1 | PESD5V0V1BL,315 |  |  |  | Diode_SMD:D_SOD-882D | https://assets.nexperia.com/documents/data-sheet/PESD5V0S1UL.pdf | C128808
D4 | 1 | LED-G |  |  |  | LED_SMD:LED_0402_1005Metric_Pad0.77x0.64mm_HandSolder | ~ | C779449
D5 | 1 | LED-R |  |  |  | LED_SMD:LED_0402_1005Metric_Pad0.77x0.64mm_HandSolder | ~ | C74338
D7 | 1 | PRTR5V0U2F,115 |  |  |  | PESD3V3L5UF115 | https://assets.nexperia.com/documents/data-sheet/PRTR5V0U2F_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 | C2937001
IC2 | 1 | XC6220B331ER-G |  |  |  | XC6220B331ER-G:XC6220B331ER-G | https://www.digikey.ph/en/products/detail/torex-semiconducto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 | C3013657
J1 | 1 | U261-241N-4BS60 |  |  |  | XKB_U261-241N-4BS60:XKB_U261-241N-4BS60_USB_C | https://www.lcsc.com/datasheet/C42418805.pdf | C319150
R1,R14 | 2 | 220R |  |  |  | Resistor_SMD:R_0402_1005Metric_Pad0.72x0.64mm_HandSolder | ~ | C2909336
R4,R3 | 1 | 10K |  |  |  | Resistor_SMD:R_0402_1005Metric_Pad0.72x0.64mm_HandSolder | ~ | C2906861
R5 | 1 | 10K | DNP |  |  | Resistor_SMD:R_0402_1005Metric_Pad0.72x0.64mm_HandSolder | ~ | C2906861
R6,R8,R9,R10,R11,R12,R2,R7 | 6 | 5.1K |  |  |  | Resistor_SMD:R_0402_1005Metric_Pad0.72x0.64mm_HandSolder | ~ | C2906874
U1 | 1 | STM32F042G6U6TR |  |  |  | Package_DFN_QFN:QFN-28_4x4mm_P0.5mm | https://www.st.com/resource/en/datasheet/stm32f042g6.pdf | C2971720

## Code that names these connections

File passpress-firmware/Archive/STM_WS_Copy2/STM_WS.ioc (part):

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Mcu.Name=STM32F042G(4-6)Ux
Mcu.Package=UFQFPN28
Mcu.UserName=STM32F042G6Ux
PA0.Mode=G1_IO1-Sampling
PA0.Signal=TSC_G1_IO1
PA1.Mode=G1_IO2-Channel
PA1.Signal=TSC_G1_IO2
PA11.Mode=Device
PA11.Signal=USB_DM
PA12.Mode=Device
PA12.Signal=USB_DP
PA2.Mode=G1_IO3-Channel
PA2.Signal=TSC_G1_IO3
PA3.Mode=G1_IO4-Channel
PA3.Signal=TSC_G1_IO4
PA4.Mode=G2_IO1-Channel
PA4.Signal=TSC_G2_IO1
PA5.Mode=G2_IO2-Channel
PA5.Signal=TSC_G2_IO2
PA6.Mode=G2_IO3-Channel
PA6.Signal=TSC_G2_IO3
PA7.Mode=G2_IO4-Sampling
PA7.Signal=TSC_G2_IO4
PB0.GPIOParameters=PinState
PB0.PinState=GPIO_PIN_SET
PB0.Signal=GPIO_Output
PB1.GPIOParameters=PinState
PB1.PinState=GPIO_PIN_SET
PB1.Signal=GPIO_Output
RCC.SYSCLKFreq_VALUE=48000000
RCC.SYSCLKSource=RCC_SYSCLKSOURCE_HSI48
board=custom
